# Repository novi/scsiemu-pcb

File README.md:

# Level Converters for SCSI-bus Emulators

This device enables you to convert logic levels between SCSI-bus and Raspberry-Pi GPIOs.

* Combine with Raspberry Pi Zero
* Supports Target(=e.g. Behaves as SCSI hard-disk) mode
* Supports Initiator, Host(=Dump data from SCSI hard-disk etc...) mode 

NOTE: Some features are depends on your SCSI emulation software.

## Compatible SCSI-bus Emulation Software

* [scsiemu](https://github.com/novi/scsiemu) [WIP]
* [akuker/RASCSI](https://github.com/akuker/RASCSI)

## Gerbers and BOM(Parts List)

* Gerber: `scsiemu-gerber/`
* BOM: `scsiemu-bom.csv`

# Related Projects

* [Tiny SCSI Emulator](https://bitbucket.org/tinyscsi/tinyscsiemulator)
* [LC-SCSI](https://github.com/pgodwin/LC-SCSI)
* [SCSI2SD](http://www.codesrc.com/mediawiki/index.php/SCSI2SD)

# License

[Attribution-ShareAlike 4.0 International (CC BY-SA 4.0)](https://creativecommons.org/licenses/by-sa/4.0/)

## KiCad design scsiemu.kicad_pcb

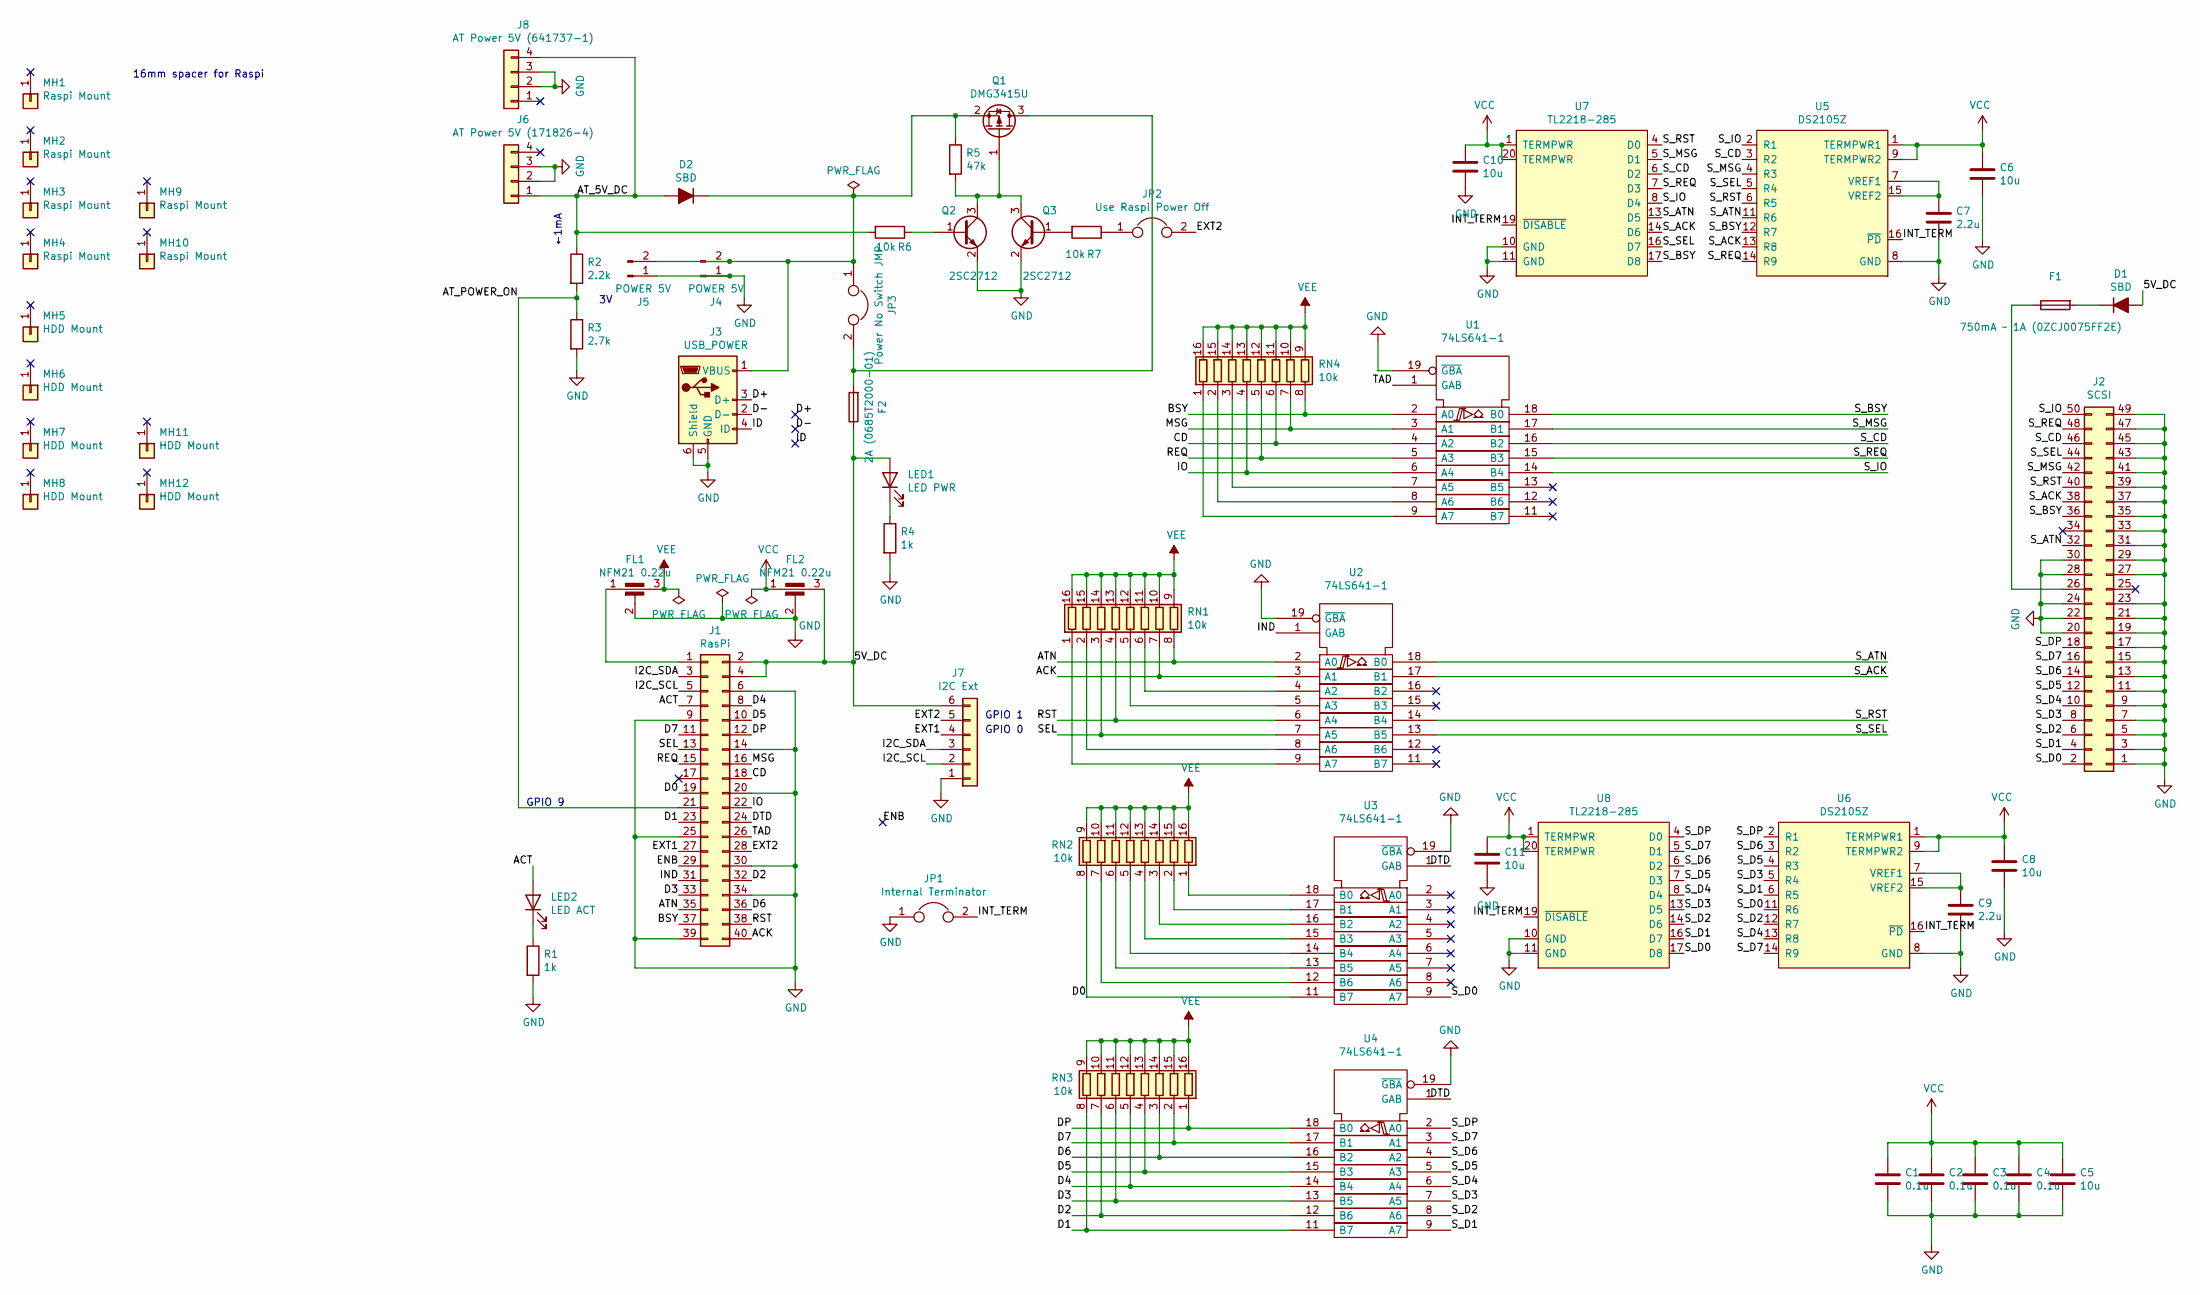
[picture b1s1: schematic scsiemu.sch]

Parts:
C1, C2, C3, C4: 0.1u; C_0603_1608Metric_Pad1.05x0.95mm_HandSolder
C5, C6, C8, C10, C11: 10u; C_1206_3216Metric_Pad1.42x1.75mm_HandSolder
C7, C9: 2.2u; C_0603_1608Metric_Pad1.05x0.95mm_HandSolder
D1, D2: SBD; D_SOD-123_HandSoldering
F1: 750mA ~~ 1A (0ZCJ0075FF2E); Fuse_1206_3216Metric_Pad1.42x1.75mm_HandSolder
F2: 2A (0685T2000-01); Fuse_1206_3216Metric_Pad1.42x1.75mm_HandSolder
FL1, FL2: NFM21 0.22u; NFM21PC
J1: RasPi; PinSocket_2x20_P2.54mm_Vertical
J2: SCSI; PinHeader_2x25_P2.54mm_Horizontal
J3: USB_POWER; USB_ZX62R-B-5P_HandSoldering
J4, J5: POWER 5V; JST_XH_B2B-XH-A_1x02_P2.50mm_Vertical
J6: AT Power 5V (171826-4); Molex_171826-4
J7: I2C Ext; JST_XH_B6B-XH-A_1x06_P2.50mm_Vertical
J8: AT Power 5V (641737-1); TE_641737-1
JP1: Internal Terminator; PinHeader_1x02_P2.54mm_Vertical
JP2: Use Raspi Power Off; SolderJumper-2_P1.3mm_Open_RoundedPad1.0x1.5mm
JP3: Power No Switch JMP; SolderJumper-2_P1.3mm_Open_RoundedPad1.0x1.5mm
LED1: LED PWR; LED_0603_1608Metric_Pad1.05x0.95mm_HandSolder
LED2: LED ACT; LED_0603_1608Metric_Pad1.05x0.95mm_HandSolder
MH1, MH2, MH3, MH4, MH9, MH10: Raspi Mount; MountingHole_2.2mm_M2
MH5, MH6, MH7, MH8, MH11, MH12: HDD Mount; MountingHole_3.5mm
Q1: DMG3415U; SOT-23_Handsoldering
Q2, Q3: 2SC2712; SOT-23_Handsoldering
R1, R4: 1k; R_0603_1608Metric_Pad1.05x0.95mm_HandSolder
R2: 2.2k; R_0603_1608Metric_Pad1.05x0.95mm_HandSolder
R3: 2.7k; R_0603_1608Metric_Pad1.05x0.95mm_HandSolder
R5: 47k; R_0603_1608Metric_Pad0.98x0.95mm_HandSolder
R6, R7: 10k; R_0603_1608Metric_Pad0.98x0.95mm_HandSolder
RN1, RN2, RN3, RN4: 10k; R_Cat16-8
U1, U2, U3, U4: 74LS641-1; SO-20_12.8x7.5mm_P1.27mm
U5, U6: DS2105Z; SOIC-16_3.9x9.9mm_P1.27mm
U7, U8: TL2218-285; TSSOP-20_4.4x6.5mm_P0.65mm

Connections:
/5V_DC: D1.2 (A), F2.1, FL2.3, J1.2, J1.4, J7.6, LED1.2 (A)
/ACK: J1.40, RN1.7 (R7.1), U2.3 (A1)
/ACT: J1.7, LED2.2 (A)
/ATN: J1.35, RN1.8 (R8.1), U2.2 (A0)
/AT_5V_DC: D2.2 (A), J6.1, J8.4, R2.1, R6.2
/AT_POWER_ON: J1.21, R2.2, R3.1
/BSY: J1.37, RN4.8 (R8.1), U1.2 (A0)
/CD: J1.18, RN4.6 (R6.1), U1.4 (A2)
/D0: J1.19, RN2.8 (R8.1), U3.11 (B7)
/D1: J1.23, RN3.8 (R8.1), U4.11 (B7)
/D2: J1.32, RN3.7 (R7.1), U4.12 (B6)
/D3: J1.33, RN3.6 (R6.1), U4.13 (B5)
/D4: J1.8, RN3.5 (R5.1), U4.14 (B4)
/D5: J1.10, RN3.4 (R4.1), U4.15 (B3)
/D6: J1.36, RN3.3 (R3.1), U4.16 (B2)
/D7: J1.11, RN3.2 (R2.1), U4.17 (B1)
/D+: J3.3 (D+)
/D-: J3.2 (D-)
/DP: J1.12, RN3.1 (R1.1), U4.18 (B0)
/DTD: J1.24, U3.1 (GAB), U4.1 (GAB)
/ENB: J1.29
/EXT1: J1.27, J7.4
/EXT2: J1.28, J7.5, JP2.2
/I2C_SCL: J1.5, J7.2
/I2C_SDA: J1.3, J7.3
/ID: J3.4 (ID)
/IND: J1.31, U2.1 (GAB)
/INT_TERM: JP1.2, U5.16 (~PD), U6.16 (~PD), U7.19 (~DISABLE), U8.19 (~DISABLE)
/IO: J1.22, RN4.4 (R4.1), U1.6 (A4)
/MSG: J1.16, RN4.7 (R7.1), U1.3 (A1)
/REQ: J1.15, RN4.5 (R5.1), U1.5 (A3)
/RST: J1.38, RN1.4 (R4.1), U2.6 (A4)
/SEL: J1.13, RN1.3 (R3.1), U2.7 (A5)
/S_ACK: J2.38, U2.17 (B1), U5.13 (R8), U7.14 (D6)
/S_ATN: J2.32, U2.18 (B0), U5.11 (R6), U7.13 (D5)
/S_BSY: J2.36, U1.18 (B0), U5.12 (R7), U7.17 (D8)
/S_CD: J2.46, U1.16 (B2), U5.3 (R2), U7.6 (D2)
/S_D0: J2.2, U3.9 (A7), U6.11 (R6), U8.17 (D8)
/S_D1: J2.4, U4.9 (A7), U6.6 (R5), U8.16 (D7)
/S_D2: J2.6, U4.8 (A6), U6.12 (R7), U8.14 (D6)
/S_D3: J2.8, U4.7 (A5), U6.5 (R4), U8.13 (D5)
/S_D4: J2.10, U4.6 (A4), U6.13 (R8), U8.8 (D4)
/S_D5: J2.12, U4.5 (A3), U6.4 (R3), U8.7 (D3)
/S_D6: J2.14, U4.4 (A2), U6.3 (R2), U8.6 (D2)
/S_D7: J2.16, U4.3 (A1), U6.14 (R9), U8.5 (D1)
/S_DP: J2.18, U4.2 (A0), U6.2 (R1), U8.4 (D0)
/S_IO: J2.50, U1.14 (B4), U5.2 (R1), U7.8 (D4)
/S_MSG: J2.42, U1.17 (B1), U5.4 (R3), U7.5 (D1)
/S_REQ: J2.48, U1.15 (B3), U5.14 (R9), U7.7 (D3)
/S_RST: J2.40, U2.14 (B4), U5.6 (R5), U7.4 (D0)
/S_SEL: J2.44, U2.13 (B5), U5.5 (R4), U7.16 (D7)
/TAD: J1.26, U1.1 (GAB)
GND: C1.2, C2.2, C3.2, C4.2, C5.2, C6.2, C7.2, C8.2, C9.2, C10.2, C11.2, FL1.2, FL2.2, J1.6, J1.9, J1.14, J1.20, J1.25, J1.30, J1.34, J1.39, J2.1, J2.3, J2.5, J2.7, J2.9, J2.11, J2.13, J2.15, J2.17, J2.19, J2.20, J2.21, J2.22, J2.23, J2.24, J2.27, J2.28, J2.29, J2.30, J2.31, J2.33, J2.35, J2.37, J2.39, J2.41, J2.43, J2.45, J2.47, J2.49, J3.5 (GND), J3.6 (Shield), J4.1, J5.1, J6.2, J6.3, J7.1, J8.2, J8.3, JP1.1, Q2.2 (E), Q3.2 (E), R1.2, R3.2, R4.2, U1.10 (GND), U1.19 (~GBA), U2.10 (GND), U2.19 (~GBA), U3.10 (GND), U3.19 (~GBA), U4.10 (GND), U4.19 (~GBA), U5.8 (GND), U6.8 (GND), U7.10 (GND), U7.11 (GND), U8.10 (GND), U8.11 (GND)
unnamed: C7.1, U5.7 (VREF1), U5.15 (VREF2)
unnamed: C9.1, U6.7 (VREF1), U6.15 (VREF2)
unnamed: D1.1 (K), F1.2
unnamed: D2.1 (K), J3.1 (VBUS), J4.2, J5.2, JP3.1, Q1.2 (S), R5.1
unnamed: F1.1, J2.26
unnamed: F2.2, JP3.2, Q1.3 (D)
unnamed: FL1.1, J1.1
unnamed: JP2.1, R7.1
unnamed: LED1.1 (K), R4.1
unnamed: LED2.1 (K), R1.1
unnamed: Q1.1 (G), Q2.3 (C), Q3.3 (C), R5.2
unnamed: Q2.1 (B), R6.1
unnamed: Q3.1 (B), R7.2
unnamed: RN1.1 (R1.1), U2.9 (A7)
unnamed: RN1.2 (R2.1), U2.8 (A6)
unnamed: RN1.5 (R5.1), U2.5 (A3)
unnamed: RN1.6 (R6.1), U2.4 (A2)
unnamed: RN2.1 (R1.1), U3.18 (B0)
unnamed: RN2.2 (R2.1), U3.17 (B1)
unnamed: RN2.3 (R3.1), U3.16 (B2)
unnamed: RN2.4 (R4.1), U3.15 (B3)
unnamed: RN2.5 (R5.1), U3.14 (B4)
unnamed: RN2.6 (R6.1), U3.13 (B5)
unnamed: RN2.7 (R7.1), U3.12 (B6)
unnamed: RN4.1 (R1.1), U1.9 (A7)
unnamed: RN4.2 (R2.1), U1.8 (A6)
unnamed: RN4.3 (R3.1), U1.7 (A5)
VCC: C1.1, C2.1, C3.1, C4.1, C5.1, C6.1, C8.1, C10.1, C11.1, FL2.1, U1.20 (VCC), U2.20 (VCC), U3.20 (VCC), U4.20 (VCC), U5.1 (TERMPWR1), U5.9 (TERMPWR2), U6.1 (TERMPWR1), U6.9 (TERMPWR2), U7.1 (TERMPWR), U7.20 (TERMPWR), U8.1 (TERMPWR), U8.20 (TERMPWR)
VEE: FL1.3, RN1.9 (R8.2), RN1.10 (R7.2), RN1.11 (R6.2), RN1.12 (R5.2), RN1.13 (R4.2), RN1.14 (R3.2), RN1.15 (R2.2), RN1.16 (R1.2), RN2.9 (R8.2), RN2.10 (R7.2), RN2.11 (R6.2), RN2.12 (R5.2), RN2.13 (R4.2), RN2.14 (R3.2), RN2.15 (R2.2), RN2.16 (R1.2), RN3.9 (R8.2), RN3.10 (R7.2), RN3.11 (R6.2), RN3.12 (R5.2), RN3.13 (R4.2), RN3.14 (R3.2), RN3.15 (R2.2), RN3.16 (R1.2), RN4.9 (R8.2), RN4.10 (R7.2), RN4.11 (R6.2), RN4.12 (R5.2), RN4.13 (R4.2), RN4.14 (R3.2), RN4.15 (R2.2), RN4.16 (R1.2)

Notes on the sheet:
←1mA
GPIO 0
GPIO 1
16mm spacer for Raspi
GPIO 9

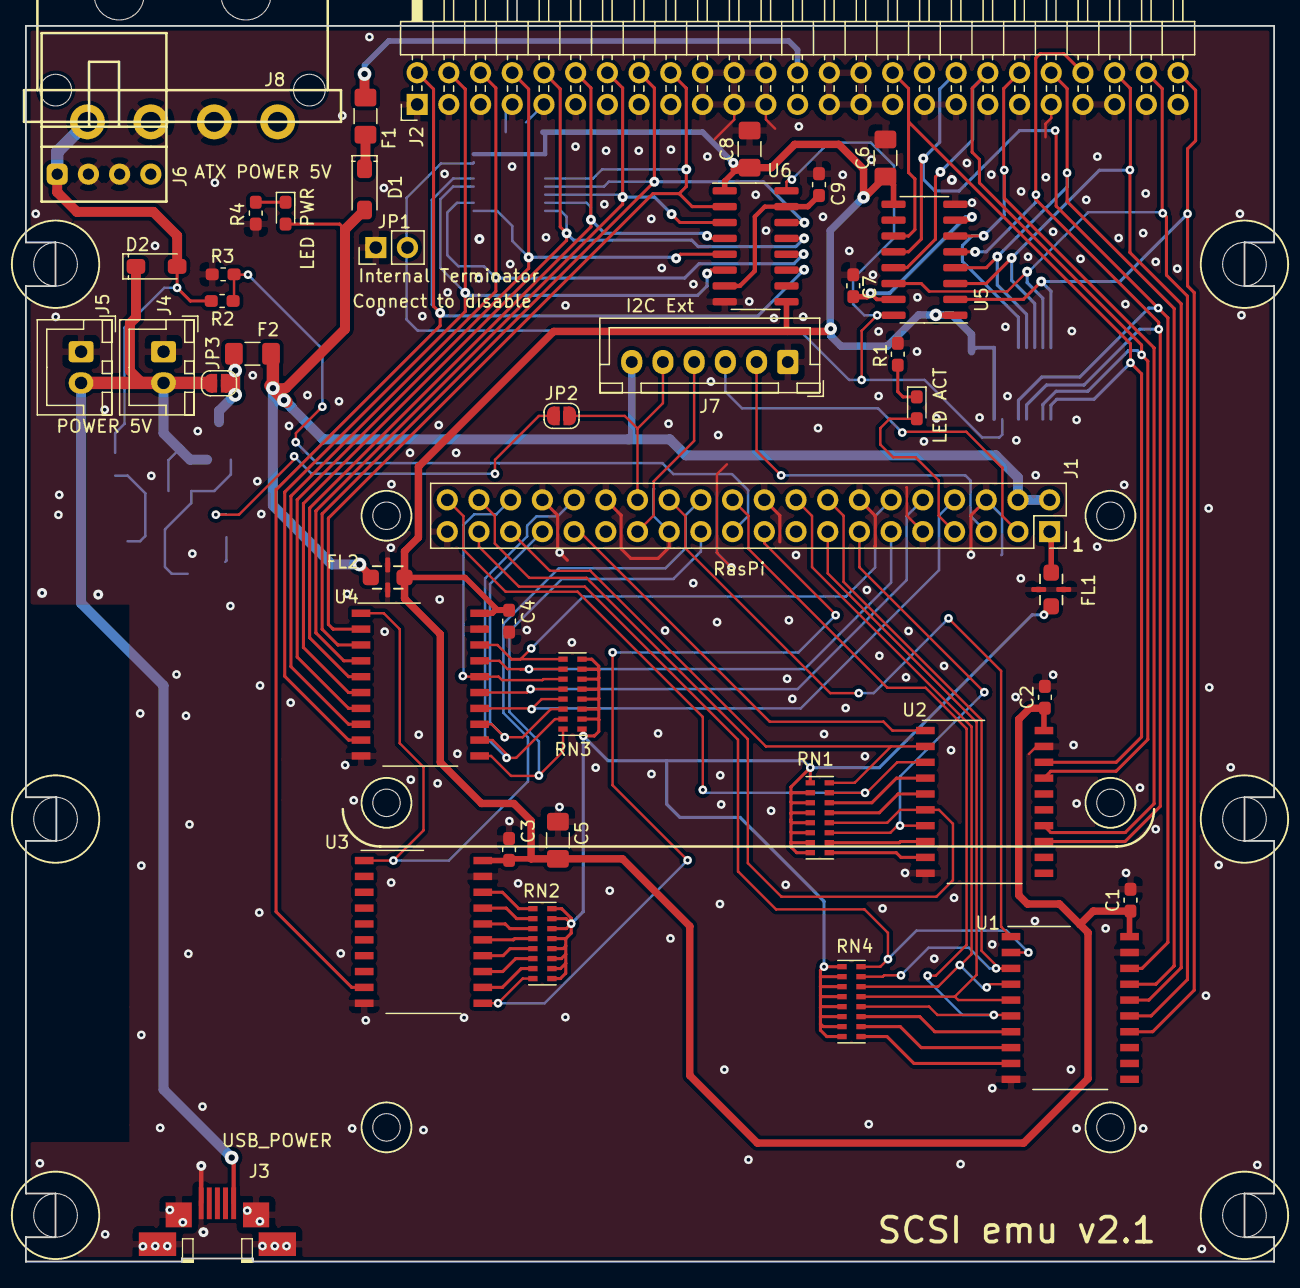
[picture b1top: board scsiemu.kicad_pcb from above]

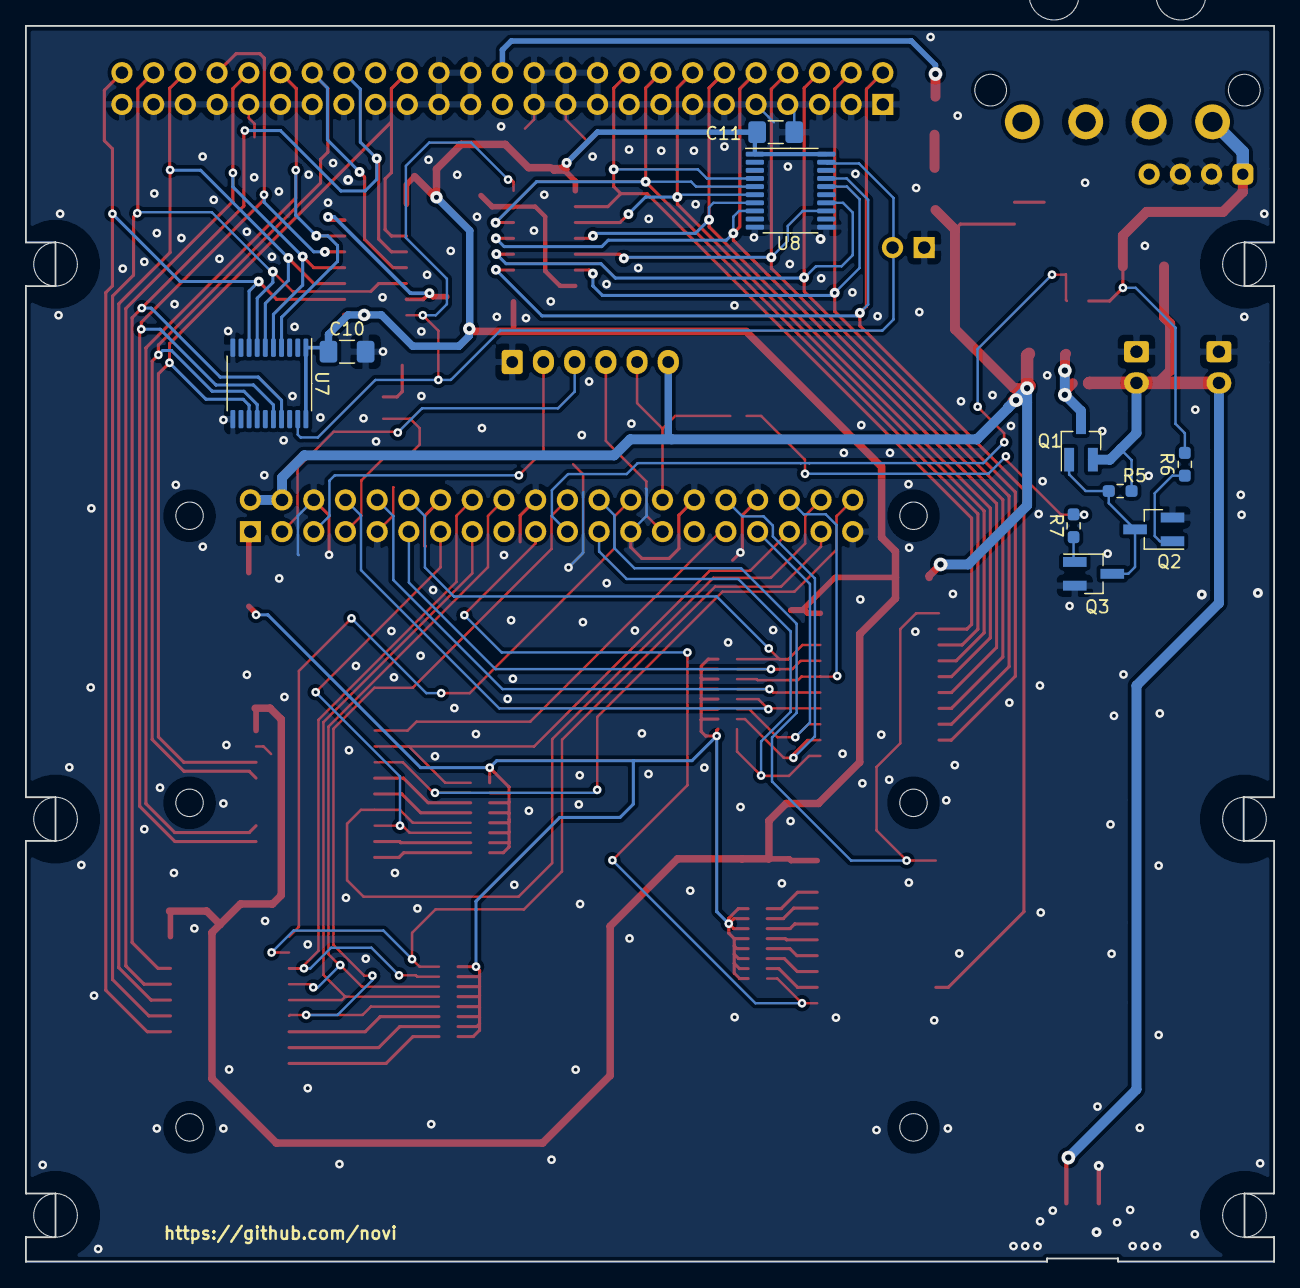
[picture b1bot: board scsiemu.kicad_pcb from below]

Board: 2 copper layers, 100.0 x 99.0 mm, 64 parts (10 on the bottom side), 78 nets.

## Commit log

2019-02-21 add KiCad projects
2020-05-16 add gerber files
2020-08-26 update lib table
2020-08-29 update libs update PCBs update schematic
2020-08-29 update track
2020-08-30 add tracks more
2020-08-30 update PCB outlines
2020-09-01 update outline
2020-09-01 add mounting holes
2020-09-12 minor update
2020-09-12 gerber exports
2020-09-13 Internal 50pin version (#1)
2020-09-26 termination on/off jumper fix GND plane
2021-04-18 add auto power off
2021-04-18 plot gerber
2021-06-05 update keepout area
